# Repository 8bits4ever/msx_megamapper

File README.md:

# RAM mapper for MSX computers

Configurable with 512K, 1MB or 2MB____

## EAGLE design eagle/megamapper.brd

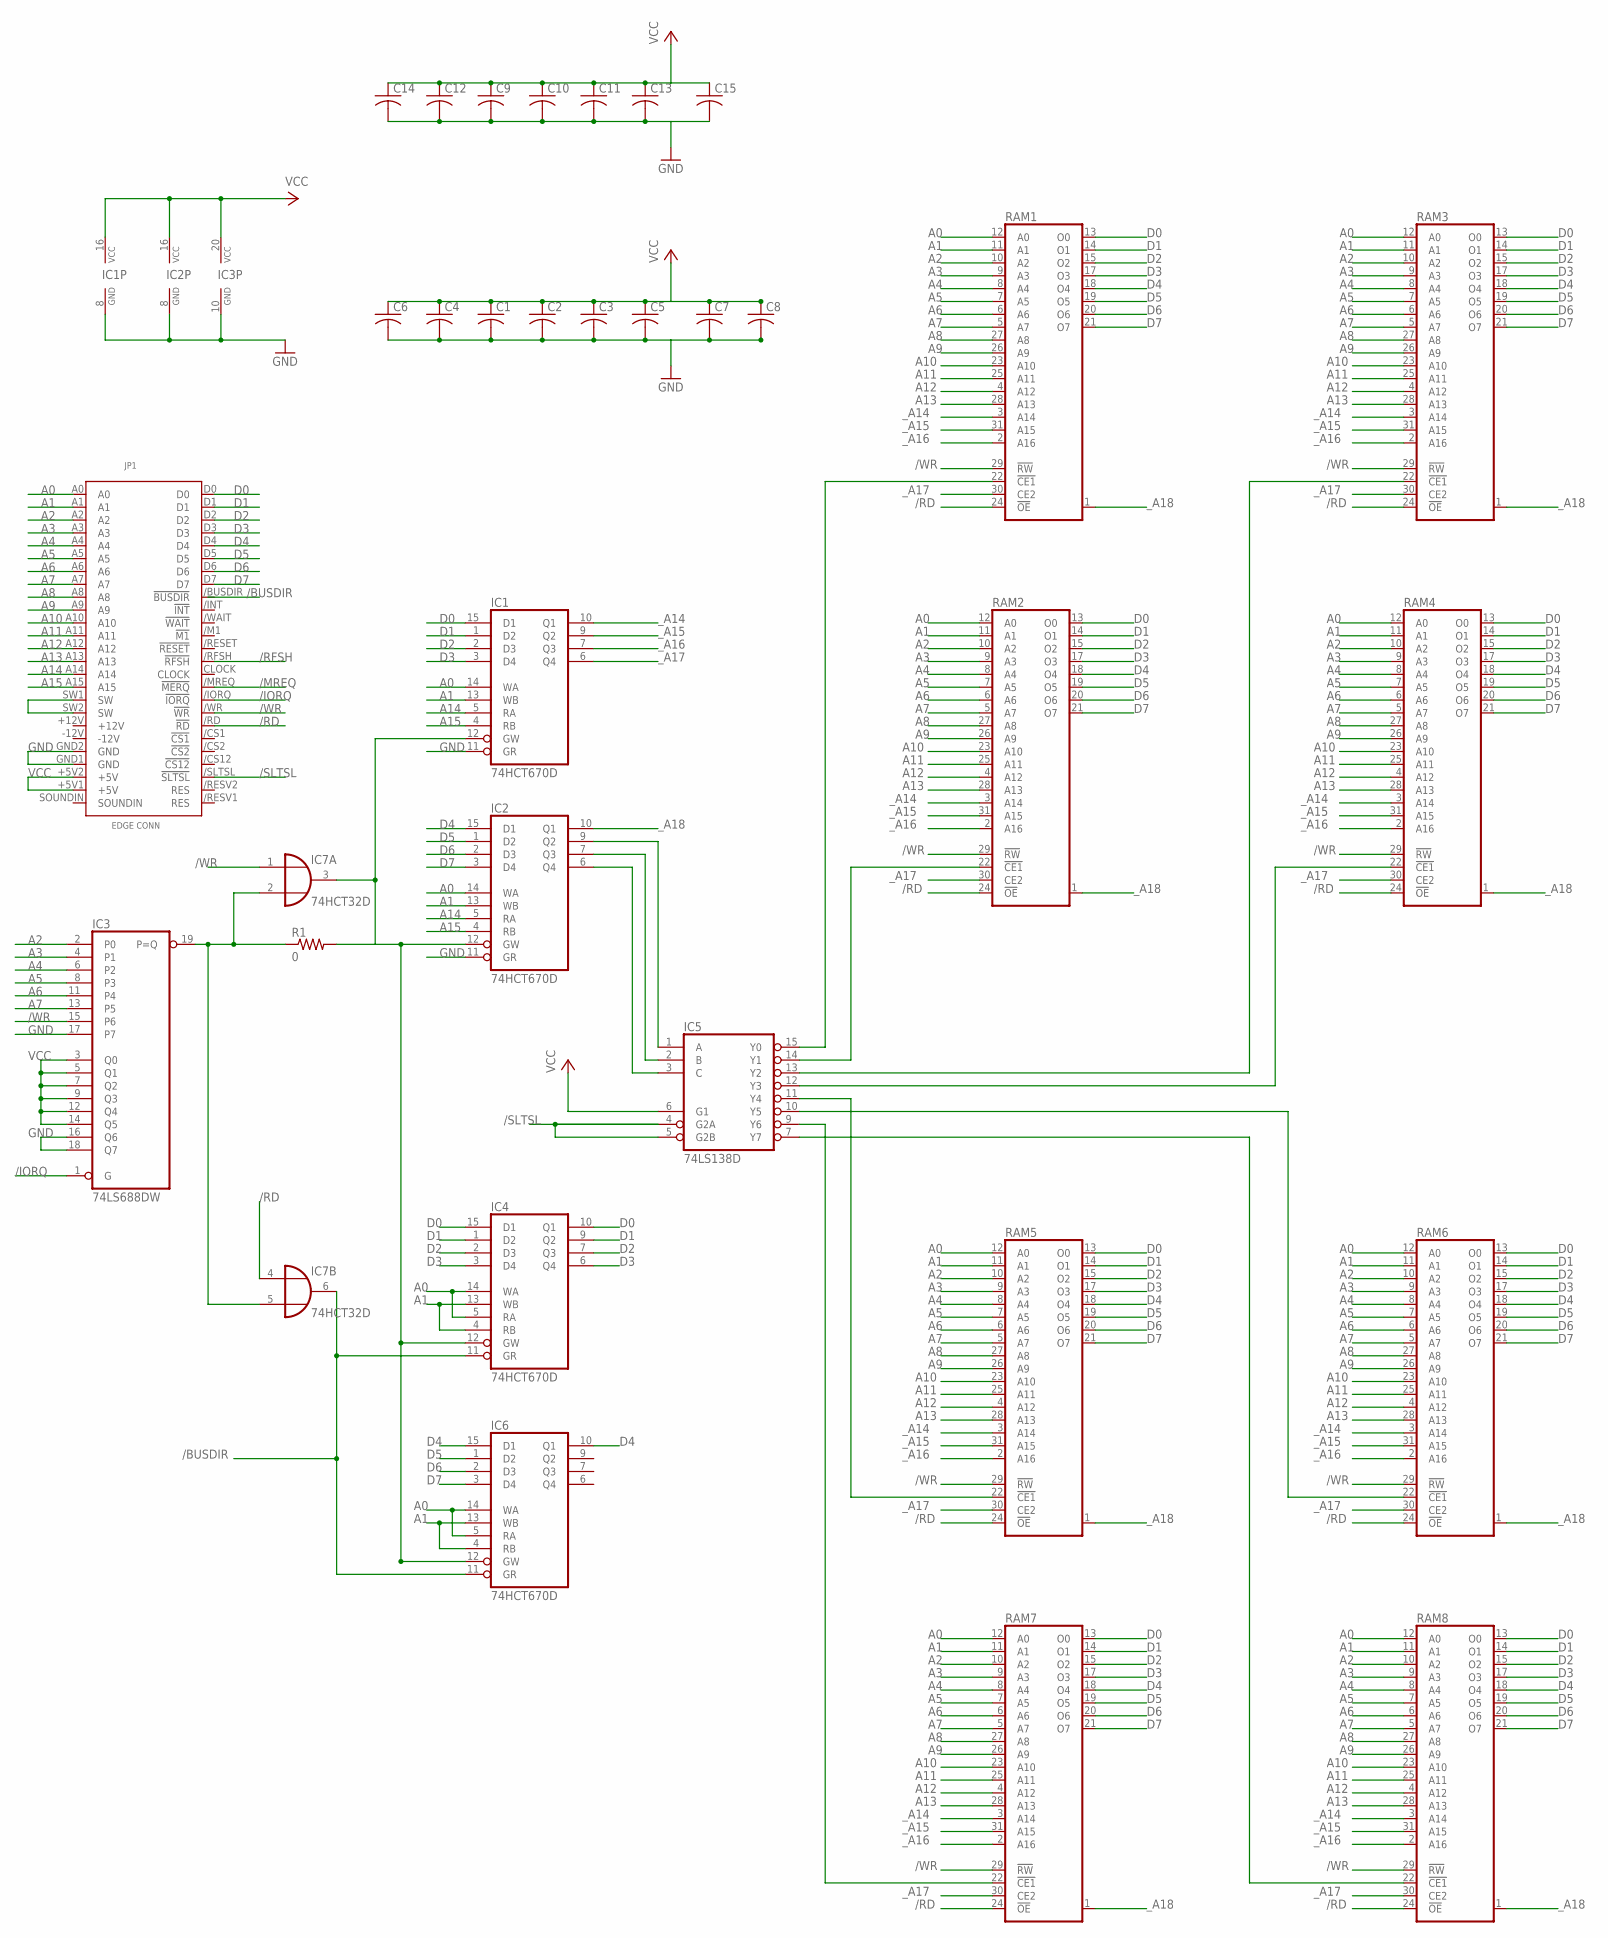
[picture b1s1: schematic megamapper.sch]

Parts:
C1, C2, C3, C4, C5, C6, C7, C8, C9, C10, C11, C12, C13, C14, C15: C-USC0805K; C0805K
IC1, IC2, IC4, IC6: 74HCT670D; SO16
IC3: 74LS688DW; SO20W
IC5: 74LS138D; SO16
IC7: 74HCT32D; SO14
JP1: MSXCART
R1: 0; R0805
RAM1, RAM2, RAM3, RAM4, RAM5, RAM6, RAM7, RAM8: TC551001CF; SOP32L

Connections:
/BUSDIR: IC4.11 (GR), IC6.11 (GR), IC7.6 (O)
/IORQ: IC3.1 (G), JP1./IORQ (!IORQ)
/MREQ: JP1./MREQ (!MERQ)
/RD: IC7.4 (I0), JP1./RD (!RD), RAM1.24 (!OE), RAM2.24 (!OE), RAM3.24 (!OE), RAM4.24 (!OE), RAM5.24 (!OE), RAM6.24 (!OE), RAM7.24 (!OE), RAM8.24 (!OE)
/RFSH: JP1./RFSH (!RFSH)
/SLTSL: IC5.4 (G2A), IC5.5 (G2B), JP1./SLTSL (!SLTSL)
/WR: IC3.15 (P6), IC7.1 (I0), JP1./WR (!WR), RAM1.29 (!RW), RAM2.29 (!RW), RAM3.29 (!RW), RAM4.29 (!RW), RAM5.29 (!RW), RAM6.29 (!RW), RAM7.29 (!RW), RAM8.29 (!RW)
A0: IC1.14 (WA), IC2.14 (WA), IC4.5 (RA), IC4.14 (WA), IC6.5 (RA), IC6.14 (WA), JP1.A0, RAM1.12 (A0), RAM2.12 (A0), RAM3.12 (A0), RAM4.12 (A0), RAM5.12 (A0), RAM6.12 (A0), RAM7.12 (A0), RAM8.12 (A0)
A1: IC1.13 (WB), IC2.13 (WB), IC4.4 (RB), IC4.13 (WB), IC6.4 (RB), IC6.13 (WB), JP1.A1, RAM1.11 (A1), RAM2.11 (A1), RAM3.11 (A1), RAM4.11 (A1), RAM5.11 (A1), RAM6.11 (A1), RAM7.11 (A1), RAM8.11 (A1)
A2: IC3.2 (P0), JP1.A2, RAM1.10 (A2), RAM2.10 (A2), RAM3.10 (A2), RAM4.10 (A2), RAM5.10 (A2), RAM6.10 (A2), RAM7.10 (A2), RAM8.10 (A2)
A3: IC3.4 (P1), JP1.A3, RAM1.9 (A3), RAM2.9 (A3), RAM3.9 (A3), RAM4.9 (A3), RAM5.9 (A3), RAM6.9 (A3), RAM7.9 (A3), RAM8.9 (A3)
A4: IC3.6 (P2), JP1.A4, RAM1.8 (A4), RAM2.8 (A4), RAM3.8 (A4), RAM4.8 (A4), RAM5.8 (A4), RAM6.8 (A4), RAM7.8 (A4), RAM8.8 (A4)
A5: IC3.8 (P3), JP1.A5, RAM1.7 (A5), RAM2.7 (A5), RAM3.7 (A5), RAM4.7 (A5), RAM5.7 (A5), RAM6.7 (A5), RAM7.7 (A5), RAM8.7 (A5)
A6: IC3.11 (P4), JP1.A6, RAM1.6 (A6), RAM2.6 (A6), RAM3.6 (A6), RAM4.6 (A6), RAM5.6 (A6), RAM6.6 (A6), RAM7.6 (A6), RAM8.6 (A6)
A7: IC3.13 (P5), JP1.A7, RAM1.5 (A7), RAM2.5 (A7), RAM3.5 (A7), RAM4.5 (A7), RAM5.5 (A7), RAM6.5 (A7), RAM7.5 (A7), RAM8.5 (A7)
A8: JP1.A8, RAM1.27 (A8), RAM2.27 (A8), RAM3.27 (A8), RAM4.27 (A8), RAM5.27 (A8), RAM6.27 (A8), RAM7.27 (A8), RAM8.27 (A8)
A9: JP1.A9, RAM1.26 (A9), RAM2.26 (A9), RAM3.26 (A9), RAM4.26 (A9), RAM5.26 (A9), RAM6.26 (A9), RAM7.26 (A9), RAM8.26 (A9)
A10: JP1.A10, RAM1.23 (A10), RAM2.23 (A10), RAM3.23 (A10), RAM4.23 (A10), RAM5.23 (A10), RAM6.23 (A10), RAM7.23 (A10), RAM8.23 (A10)
A11: JP1.A11, RAM1.25 (A11), RAM2.25 (A11), RAM3.25 (A11), RAM4.25 (A11), RAM5.25 (A11), RAM6.25 (A11), RAM7.25 (A11), RAM8.25 (A11)
A12: JP1.A12, RAM1.4 (A12), RAM2.4 (A12), RAM3.4 (A12), RAM4.4 (A12), RAM5.4 (A12), RAM6.4 (A12), RAM7.4 (A12), RAM8.4 (A12)
A13: JP1.A13, RAM1.28 (A13), RAM2.28 (A13), RAM3.28 (A13), RAM4.28 (A13), RAM5.28 (A13), RAM6.28 (A13), RAM7.28 (A13), RAM8.28 (A13)
A14: IC1.5 (RA), IC2.5 (RA), JP1.A14
A15: IC1.4 (RB), IC2.4 (RB), JP1.A15
D0: IC1.15 (D1), IC4.10 (Q1), IC4.15 (D1), JP1.D0, RAM1.13 (O0), RAM2.13 (O0), RAM3.13 (O0), RAM4.13 (O0), RAM5.13 (O0), RAM6.13 (O0), RAM7.13 (O0), RAM8.13 (O0)
D1: IC1.1 (D2), IC4.1 (D2), IC4.9 (Q2), JP1.D1, RAM1.14 (O1), RAM2.14 (O1), RAM3.14 (O1), RAM4.14 (O1), RAM5.14 (O1), RAM6.14 (O1), RAM7.14 (O1), RAM8.14 (O1)
D2: IC1.2 (D3), IC4.2 (D3), IC4.7 (Q3), JP1.D2, RAM1.15 (O2), RAM2.15 (O2), RAM3.15 (O2), RAM4.15 (O2), RAM5.15 (O2), RAM6.15 (O2), RAM7.15 (O2), RAM8.15 (O2)
D3: IC1.3 (D4), IC4.3 (D4), IC4.6 (Q4), JP1.D3, RAM1.17 (O3), RAM2.17 (O3), RAM3.17 (O3), RAM4.17 (O3), RAM5.17 (O3), RAM6.17 (O3), RAM7.17 (O3), RAM8.17 (O3)
D4: IC2.15 (D1), IC6.10 (Q1), IC6.15 (D1), JP1.D4, RAM1.18 (O4), RAM2.18 (O4), RAM3.18 (O4), RAM4.18 (O4), RAM5.18 (O4), RAM6.18 (O4), RAM7.18 (O4), RAM8.18 (O4)
D5: IC2.1 (D2), IC6.1 (D2), JP1.D5, RAM1.19 (O5), RAM2.19 (O5), RAM3.19 (O5), RAM4.19 (O5), RAM5.19 (O5), RAM6.19 (O5), RAM7.19 (O5), RAM8.19 (O5)
D6: IC2.2 (D3), IC6.2 (D3), JP1.D6, RAM1.20 (O6), RAM2.20 (O6), RAM3.20 (O6), RAM4.20 (O6), RAM5.20 (O6), RAM6.20 (O6), RAM7.20 (O6), RAM8.20 (O6)
D7: IC2.3 (D4), IC6.3 (D4), JP1.D7, RAM1.21 (O7), RAM2.21 (O7), RAM3.21 (O7), RAM4.21 (O7), RAM5.21 (O7), RAM6.21 (O7), RAM7.21 (O7), RAM8.21 (O7)
GND: C1.2, C2.2, C3.2, C4.2, C5.2, C6.2, C7.2, C8.2, C9.2, C10.2, C11.2, C12.2, C13.2, C14.2, C15.2, IC1.8 (GND), IC1.11 (GR), IC2.8 (GND), IC2.11 (GR), IC3.10 (GND), IC3.16 (Q6), IC3.17 (P7), IC3.18 (Q7), IC4.8 (GND), IC5.8 (GND), IC6.8 (GND), IC7.7 (GND), JP1.GND1 (GND), JP1.GND2 (GND), RAM1.16 (GND), RAM2.16 (GND), RAM3.16 (GND), RAM4.16 (GND), RAM5.16 (GND), RAM6.16 (GND), RAM7.16 (GND), RAM8.16 (GND)
unnamed: IC1.12 (GW), IC2.12 (GW), IC4.12 (GW), IC6.12 (GW), IC7.3 (O), R1.2
unnamed: IC5.14 (Y1), RAM2.22 (!CE1)
unnamed: IC5.13 (Y2), RAM3.22 (!CE1)
unnamed: IC5.12 (Y3), RAM4.22 (!CE1)
unnamed: IC5.11 (Y4), RAM5.22 (!CE1)
unnamed: IC5.10 (Y5), RAM6.22 (!CE1)
unnamed: JP1.SW1 (SW), JP1.SW2 (SW)
unnamed: IC2.9 (Q2), IC5.1 (A)
unnamed: IC2.7 (Q3), IC5.2 (B)
unnamed: IC2.6 (Q4), IC5.3 (C)
unnamed: IC5.9 (Y6), RAM7.22 (!CE1)
unnamed: IC5.7 (Y7), RAM8.22 (!CE1)
unnamed: IC3.19 (P=Q), IC7.2 (I1), IC7.5 (I1), R1.1
unnamed: IC5.15 (Y0), RAM1.22 (!CE1)
VCC: C1.1, C2.1, C3.1, C4.1, C5.1, C6.1, C7.1, C8.1, C9.1, C10.1, C11.1, C12.1, C13.1, C14.1, C15.1, IC1.16 (VCC), IC2.16 (VCC), IC3.3 (Q0), IC3.5 (Q1), IC3.7 (Q2), IC3.9 (Q3), IC3.12 (Q4), IC3.14 (Q5), IC3.20 (VCC), IC4.16 (VCC), IC5.6 (G1), IC5.16 (VCC), IC6.16 (VCC), IC7.14 (VCC), JP1.+5V1 (+5V), JP1.+5V2 (+5V), RAM1.32 (VCC), RAM2.32 (VCC), RAM3.32 (VCC), RAM4.32 (VCC), RAM5.32 (VCC), RAM6.32 (VCC), RAM7.32 (VCC), RAM8.32 (VCC)
_A14: IC1.10 (Q1), RAM1.3 (A14), RAM2.3 (A14), RAM3.3 (A14), RAM4.3 (A14), RAM5.3 (A14), RAM6.3 (A14), RAM7.3 (A14), RAM8.3 (A14)
_A15: IC1.9 (Q2), RAM1.31 (A15), RAM2.31 (A15), RAM3.31 (A15), RAM4.31 (A15), RAM5.31 (A15), RAM6.31 (A15), RAM7.31 (A15), RAM8.31 (A15)
_A16: IC1.7 (Q3), RAM1.2 (A16), RAM2.2 (A16), RAM3.2 (A16), RAM4.2 (A16), RAM5.2 (A16), RAM6.2 (A16), RAM7.2 (A16), RAM8.2 (A16)
_A17: IC1.6 (Q4), RAM1.30 (CE2), RAM2.30 (CE2), RAM3.30 (CE2), RAM4.30 (CE2), RAM5.30 (CE2), RAM6.30 (CE2), RAM7.30 (CE2), RAM8.30 (CE2)
_A18: IC2.10 (Q1), RAM1.1 (NC), RAM2.1 (NC), RAM3.1 (NC), RAM4.1 (NC), RAM5.1 (NC), RAM6.1 (NC), RAM7.1 (NC), RAM8.1 (NC)

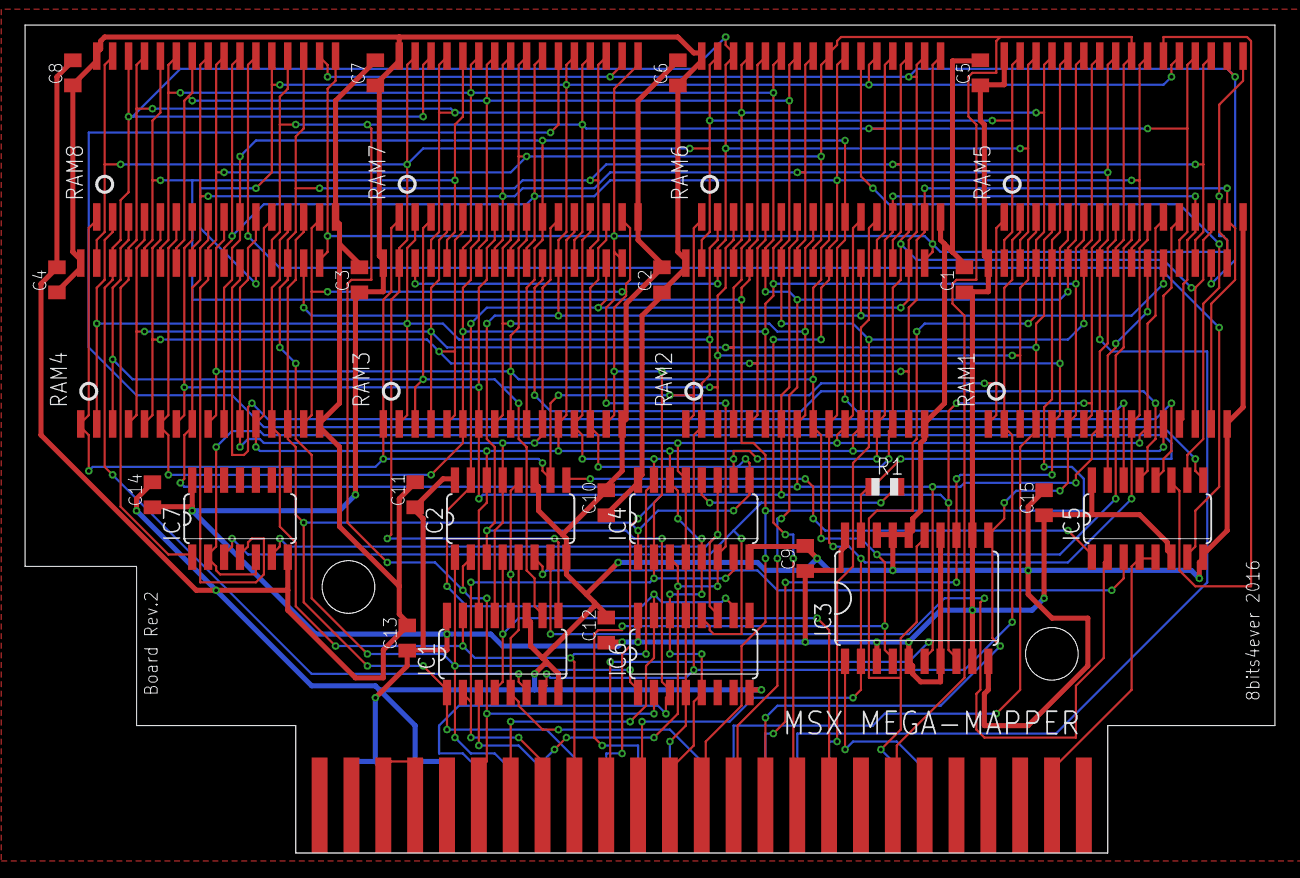
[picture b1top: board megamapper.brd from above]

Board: 2 copper layers, 99.7 x 66.0 mm, 32 parts (0 on the bottom side), 50 nets.

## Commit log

2021-08-08 Create dummy
2021-08-08 Rename megamapper.brd to eagle/megamapper.brd
2021-08-08 Rename megamapper.sch to eagle/megamapper.sch
